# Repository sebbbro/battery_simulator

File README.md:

A battery simulator project created in Eagle. The sym.sch file contains the circuit diagram, while the sym.brd file contains the board design.

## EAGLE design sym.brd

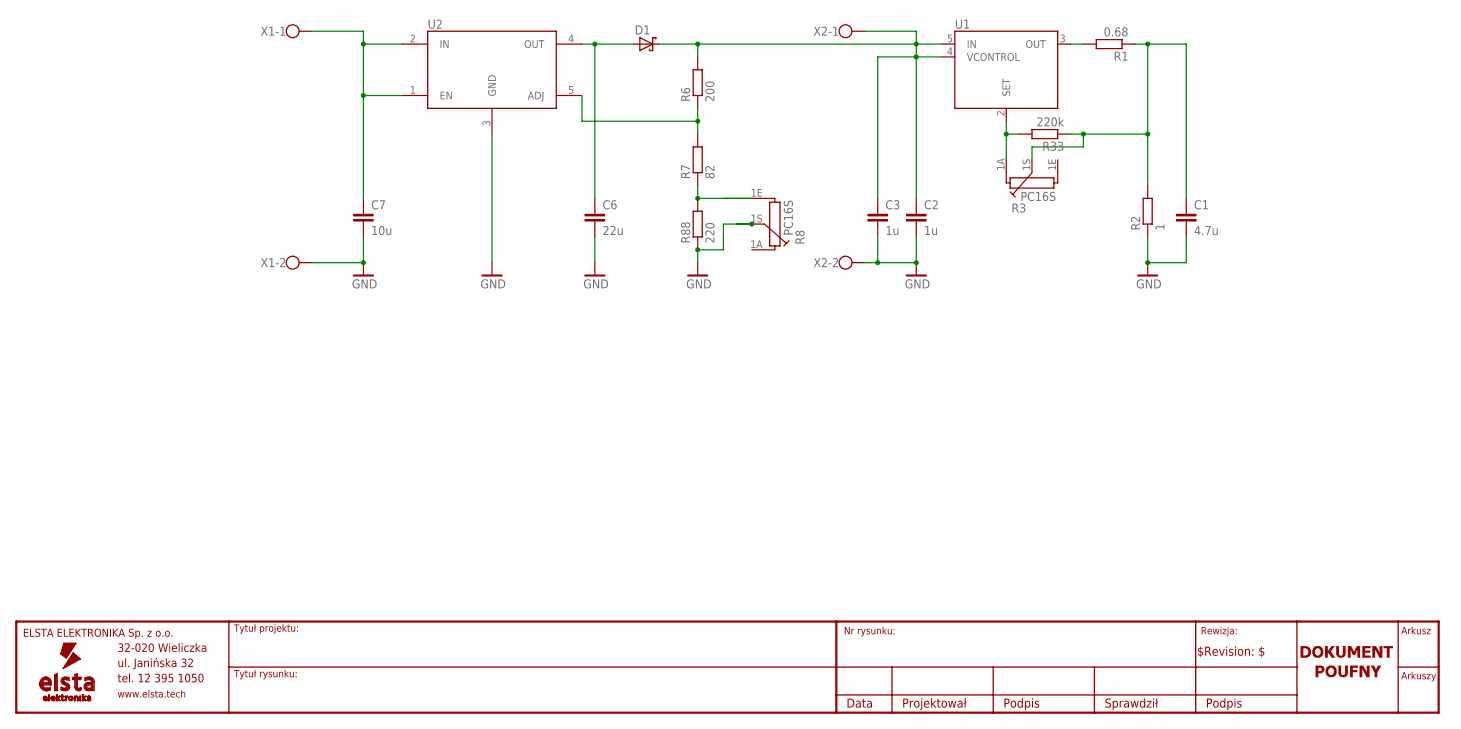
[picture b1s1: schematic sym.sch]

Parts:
C1: 4.7u; C1206
C2, C3: 1u; C1206
C6: 22u; C1206
C7: 10u; C1206
D1: 1N5821; D0,6
R1: 0.68; 0617/17
R2: 1; 0617/17
R3, R8: PC16S
R6: 200; R1206
R7: 82; R1206
R33: 220k; R1206
R88: 220; R0805
U1: LT3080ET/IT; TO-220-5
U2: MIC29302WT; TO-220-5
X1, X2: W237-02P; W237-132

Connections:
GND: C1.2, C2.2, C3.2, C6.2, C7.2, R2.1, R8.1S, R88.1, U2.3 (GND), X1.2, X2.2
unnamed: R7.1, R8.1E, R88.2
unnamed: R3.1A, R33.2, U1.2 (SET)
unnamed: C6.1, D1.A, U2.4 (OUT)
unnamed: R6.1, R7.2, U2.5 (ADJ)
unnamed: R1.2, U1.3 (OUT)
unnamed: C1.1, R1.1, R2.2, R3.1S, R33.1
unnamed: C2.1, C3.1, D1.C, R6.2, U1.4 (VCONTROL), U1.5 (IN), X2.1
unnamed: C7.1, U2.1 (EN), U2.2 (IN), X1.1

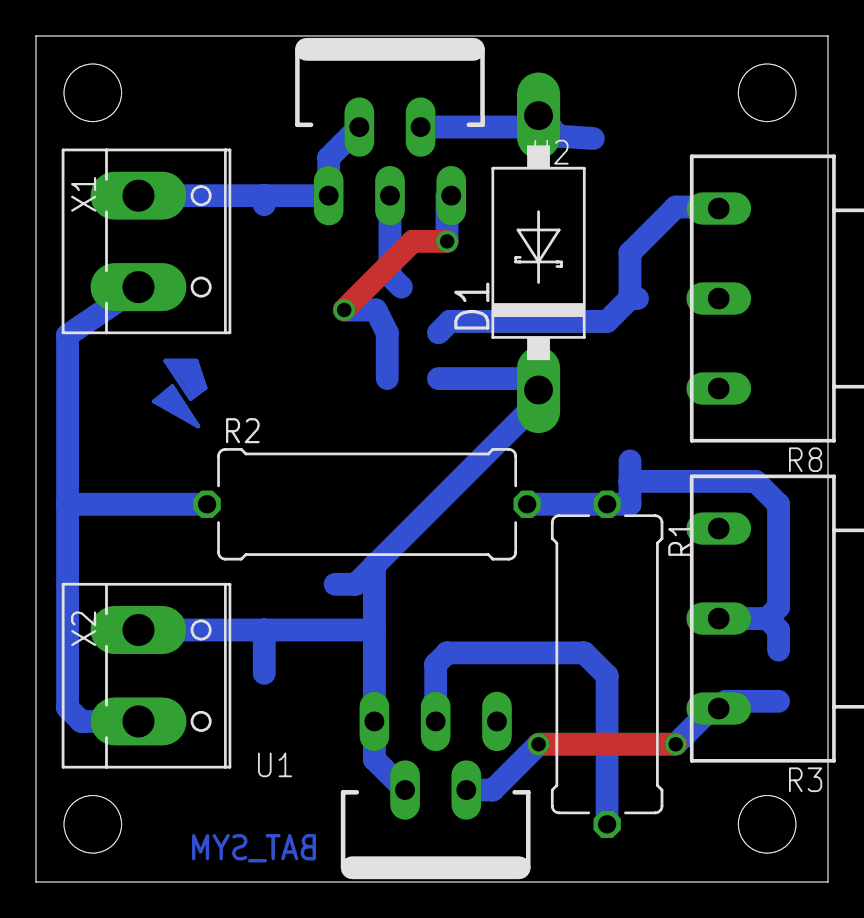
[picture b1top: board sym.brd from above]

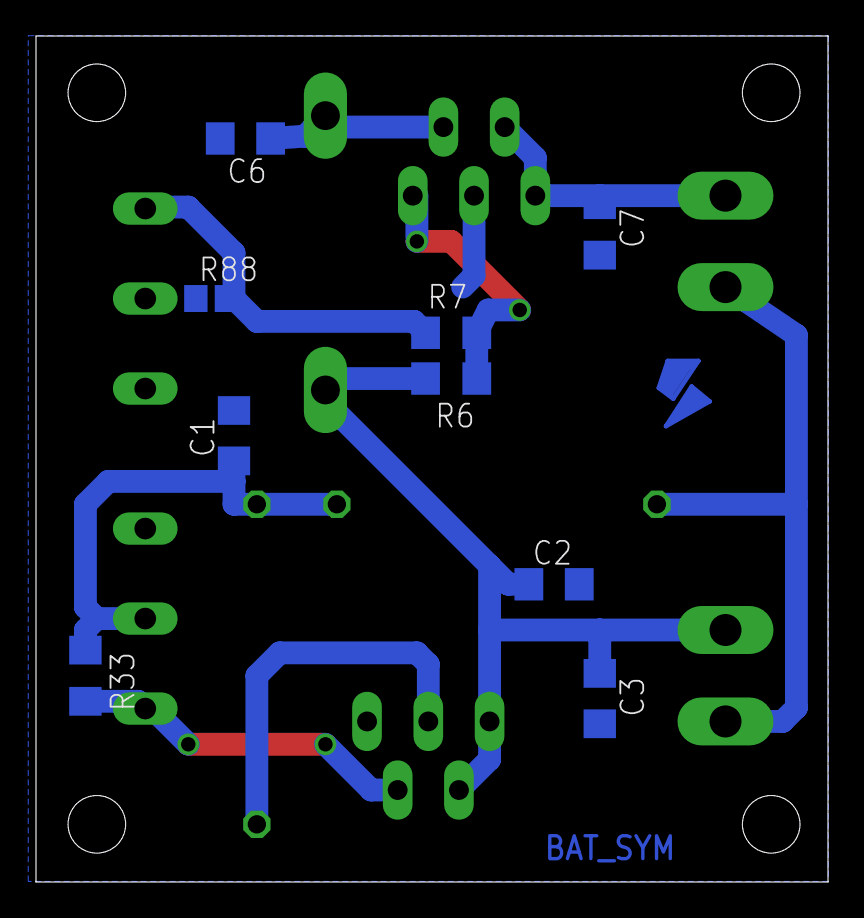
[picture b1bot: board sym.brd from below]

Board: 2 copper layers, 44.0 x 47.0 mm, 21 parts (10 on the bottom side), 9 nets.

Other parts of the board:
U$1: A4_LANDSCAPE_2:1_TOP
U$2: EE_LOGO_LIGHTNING
U$3: A4_LANDSCAPE_2:1_BOTTOM
